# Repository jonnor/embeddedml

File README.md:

# Machine learning on embedded devices

Focused primarily on running inference/prediction/feed-forward part on a microcontroller (or small embedded device).
Training phase can run on a standard computer/server, using existing tools as much as possible.

# Background

## What and when to use machine learning

The defaults right now are to do conventional signal processing (no learning) in sensor,
and stream raw data to the cloud for storage and processing. Machine learning happens in the cloud.
If gateways are used, they mostly forward communication (no data processing). 

On-edge processing valueable when

* Local response needed. Autonomy
* Adaptable response needed. Over time, in context.
* Low/predictable latency needed
* Sending raw sensor data has privacy implications.
Audio, video.
* Unreliable connection
* High bandwidth sensor input.
Audio, video, accelerometer/IMU, current sensor, radiowaves.
* Low bandwidth algorithm output
* Events of interest are rare
* Low energy usage needed
* Full/raw sensor data is not valuable to store
* Sensor system should be low cost

Example usecases

* Predictive maintenance, using audio/vibration data
* Activitity detection for people, using audio/accelerometer data. Assistive tech, medical
* Appliance disaggregation, using aggregated power consumption data. "Non-Intrusive Load Monitoring" (NILM)
* Anomaly/change detection for predictive maintenance, using audio/vibration data, or electrical data
* Gesture recognition as human input device, using accelerometer/gyro data.
* Speech/command recognition as human input device, using microphone. Keyword/Wake-word detection
* Battery saving in wireless sensors. Normally sending day/week aggregates, on event/anomaly detection send data immediately
* Health status of animals via activity detected using accelerometer
* Monitoring eating activity using accelerometer [1](https://www.sciencedirect.com/science/article/pii/S0010482515000086)
* Environmental monitoring, using microphone to detect unwanted activity like cutting down trees
* Adaptive signalling and routing for wireless transmission in Wireless Sensor networks
* Electronic nose using arrays of MEMS detectors
* Material identification using reflecive spectrometer [1](https://hackaday.io/project/143014-compact-25-spectrometer/)

More notes on [Applications](./applications)

### Motivation

* [Why the Future of Machine Learning is Tiny (devices)](https://petewarden.com/2018/06/11/why-the-future-of-machine-learning-is-tiny)
Tiny Computers are Already Cheap and Everywhere. Energy is the Limiting Factor.We Capture Much More Sensor Data Than We Use.
* [embedded.com: Bringing machine learning to the edge](https://www.embedded.com/electronics-blogs/say-what-/4460873/Bringing-machine-learning-to-the-edge--A-Q-A-with-Neurala-s-Anatoli-Gorshechnikov-)
Predictions are much lower bandwidth than the raw sensor data (e.g. video)
It allows for local adaptation in the AI logic (L-DNN)
It achieves lower latency between observed event and action resulting from AI logic
"the most important question is what is the least amount accuracy and computation complexity we can do
while still delivering the business value?"
Top mistake: "Continuing with the top down approach ‘let’s make it perform the task first and then squeeze it on device`
instead of switching to bottom up ‘let’s make it run on device and fulfill all hardware constraints first,
and then tune it for the task at hand’."
* [How to run deep learning model on microcontroller with CMSIS-NN](https://www.dlology.com/blog/how-to-run-deep-learning-model-on-microcontroller-with-cmsis-nn/).
Why run deep learning model on a microcontroller?
Sensitive data gets to the cloud, photos, and audio recordings.
The company who sells this may charge a service fee to use its service and even worse sell your private data.
It won't work without the network connection to the server.
Data traveling back and forth between the device and server introduces lag.
Require network and wireless hardware components on the circuit design which increase the cost.
It might waste bandwidth sending useless data.

# Own contributions

Presentations

- [Embedding Data Science in IoT devices with MicroPython and emlearn](./presentations/euroscipy2026/presentation). EuroSciPy 2026, Krakow.
- [Machine Learning on Microcontrollers; Tiny, Useful and Fun](./presentations/ai-dev-europe-2025). Open Source GenAI & ML Summit. Amsterdam, August 2025.
- [Sensor data processing for scientific applications with MicroPython](./presentations/euroscipy2025/). EuroSciPy 2025, Krakow.
- [Machine Learning on Microcontrollers With Zephyr and emlearn](./presentations/open-source-summit-europe-2025). Open Source Summit / Zephyr Developer Summit. Amsterdam, August 2025.
- [Microcontrollers and Machine Learning with MicroPython and emlearn](./presentations/foss-north-2025). FOSS-North. Gothenburg, April 2025.
- [Sensor data processing on microcontrollers with MicroPython and emlearn](./presentations/PyConZA2024/). PyCon South Africa. Online, October 2024.
- [emlearn - Machine Learning for Tiny Embedded Systems](./presentations/EmbeddedOnlineConference2024). Embedded Online Conference. April 2024.
- [6 years of open source TinyML with emlearn](./presentations/TinymlEMEA2024). TinyML EMEA, Milano. June 2024.
- [emlearn - Machine Learning for Tiny Embedded Systems](./presentations/EmbeddedOnlineConference2024). May 2024.
- [Machine Learning on microcontrollers using MicroPython and emlearn](./presentations/PyDataBerlin2024/). PyDataBerlin & PyCon DE. April 2024.
- [HVAC monitoring in commercial buildings using Anomaly Detection](./presentations/TinymlAnomalyDetection2023/). TinyAI Forum on PdM and Anomaly Detection (online). December 2023.

Lecture notes

- [Practical TinyML with emlearn](./presentations/AarhusUniversity2026/). Aarhus University. March 2026.
- [emlearn @ TinyMLDays Aarhus](./presentations/TinyMLDays2025/). August 2025.

Open source software

- [emlearn](https://github.com/emlearn/emlearn). Machine Learning inference engine in C99 for Microcontrollers and Embedded devices. Since 2018.
- [emlearn-micropython](https://github.com/emlearn/emlearn-micropython). Efficient and convenient Machine Learning and DSP for MicroPython. Since 2024.

Fun projects

- Automatic toothbrush timer using accelerometer. [Github project](https://github.com/jonnor/toothbrush/). [Video presentation](https://www.youtube.com/watch?v=KkrfKPlnoZQ).
- Spectrometer for edible oils [Github project](https://github.com/jonnor/spectrometer/).

Commercial projects

- Acoustic detection of first crack in [Roest coffee roasting machines](https://www.roestcoffee.com/). Shipping since 2019.
[Tech presentation](https://www.youtube.com/watch?v=muZY1eCke40). 

# Learning material

Books

* [Learning in Embedded Systems](https://mitpress.mit.edu/books/learning-embedded-systems), May 1993.
* [TinyML: Machine Learning with TensorFlow on Arduino, and Ultra-Low Power Micro-Controllers](https://tinymlbook.com/). January, 2020.
* [TinyML Cookbook](https://www.packtpub.com/product/tinyml-cookbook/9781801814973).
* [Machine Learning Systems - Principles and Practices of Engineering Artificially Intelligent Systems](https://mlsysbook.ai/book/).

Articles

- [Embedded.com: Applying machine learning in embedded systems](https://www.embedded.com/applying-machine-learning-in-embedded-systems)
- [Embedded.com: Transfer learning for the IoT](https://www.embedded.com/transfer-learning-for-the-iot/)

# Tools

Open-source

* [emlearn](http://github.com/emlearn/emlearn). Inference engine for microcontrollers.
Supports converting scikit-learn models to plain C code.
No dynamic allocations. No runtime needed.
* [TensorFlow Lite for Microcontrollers](https://www.tensorflow.org/lite/microcontrollers).
Supports neural network models made with TensorFlow (including Keras).
Can run on wide range of platforms.
Since November 2018. Supports ARM Cortex M, RISC-V, ESP32/Xtensa and Linux/MacOS host.
Requires a runtime, aroud 20 kB.
* [onnx2c](https://github.com/kraiskil/onnx2c). Allows generating C code from ONNX models.
* [iree](https://iree.dev/guides/deployment-configurations/bare-metal/). Compiler. Has bare metal target. Around 30 kB runtime.
* [executorch](https://github.com/pytorch/executorch).
C++ framework for deploying PyTorch models. Focused on custom backends, NPUs etc. Microcontroller CPU less in focus.
Around 50 kB runtime. Supports bare-metal via "Portable" operations, or specialized for Cortex M.
* [nnom](https://github.com/majianjia/nnom) - Fixed-point neural network compiler for microcontrollers.
Supports wide range of networks. Outputs plain C code. Can use CMSIS-NN on ARM Cortex M.
* [Embedded Learning Library](https://github.com/Microsoft/ELL) by Microsoft. Discontinued in 2024
Set of C++ libraries for machine learning on embedded platforms. Includes code for kNN, RandomForest etc.
Also has some node-based dataflow system in place it seems. JavaScript and Python bindings.
* [uTensor](https://github.com/uTensor/uTensor).
Export Tensorflow model to mbed/ARM microcontrollers.
Not supported on ESP32 or RISC-V or similar. Lower activity since 2021.
- [sklearn-porter](https://github.com/nok/sklearn-porter).
Can compile DecisionTreeClassifier and SVC models to C.
Uses dynamic memory.
Not optimized for use on embedded devices.
* [microTVM](https://tvm.apache.org/docs/topic/microtvm/index.html).
Depends only on the C standard library, and runs bare metal such as STM32 and NRF52 microcontrollers.
Is under development. Which models are supported on microcontrollers not specified.

Low-level libraries

* [gemmlowp](https://github.com/google/gemmlowp).
Low-precision matrix multiplication. Only general matrix multiplication ("GEMM"). C++11
* [CMSIS-NN](https://github.com/ARM-software/CMSIS-NN). Neural network operations for ARM Cortex M.
* [esp-nn](https://github.com/espressif/esp-nn). Neural Network functions Espressif ESP32 (Xtensa and RISC-V).
* . Can be used bare-metal, but more focused on mobile/server grade (Cortex A+ etc).

Proprietary

* X-CUBE-AI for STM32

Historical

- [nn4mc_cpp](https://github.com/correlllab/nn4mc_cpp).
Neural Networks for Microcontrollers.
Supports Keras natively. Provides instructions for PyTorch et.c via ONNX.
Documentation for using from Python is lacking, as well as the type of networks supported.
Does not seem maintained since 2020.
* [Embedded Classification Software Toolbox](https://github.com/ma2th/ecst).
Unmaintained since 2018.
* ONNC project has a [backend for ARM Cortex M](https://github.com/ONNC/onnc-tutorial/blob/master/lab_2_Digit_Recognition_with_ARM_CortexM/lab_2.md) (using CMSIS-NN)
and a [C backend](https://github.com/ONNC/onnc/blob/74e59908b2881844329c3d330eea7a7c306e1e22/docs/ONNC-C-Backend-Guide.md).
Allows to convert an ONNX models to run on devices.
Not updated since 2021.
- [micromlgen](https://github.com/eloquentarduino/micromlgen).
Generate C code for microcontrollers from Python's sklearn classifiers.
Archived in 2024.

# Models

A range of Machine Learning models are useful in an embedded devices setting.
Classical methods are used when the amount of data is quite small,
and neural networks for large datasets and complex inputs.

Below are notes on the various models in the context of embedded Machine Learning,
including model size and compute-time optimization.

- [Tree-based methods](./models/tree-based.md).
Random Forest, Extratrees, Decision Trees, et.c.
- [Neural Networks](./models/neural-networks.md).
Convolutional Neural Networks (CNN), Recurrent Neural Networks (RNN), Autoencoders
- [Support Vector Machines](./models/support-vector-machine.md) (SVM).
- [Mixture models](./models/mixtures.md).
Gaussian Mixture Models (GMM).
- [Nearest Neighbours](./models/k-nearest-neighbours.md). kNN et.c.

# More topics

- [Privacy](./topics/privacy.md)
- [Energy usage](./topics/energy-usage.md)
- [Model size](./topics/model-size.md)
- [On-device learning](./on-device-learning)

## State of the Art in 2019
Of ML inference on general-purpose microcontrollers.

```
TODO: update for 2023
```

- Deep models have efficient implementations for ARM Cortex-M. Ex: CNN and RNN in CMSIS-NN, FC in uTensor
- Some implementations available for non-neural models that *can* be used. Ex: SVM,RF,AdaBoost in sklearn-porter
- A few special-designed ML algorithms made. Ex: ProtoNN, Bonsai
- Basic tools available for converting Tensorflow models
- Keyword-spotting/wake-word on audio well established. Used in commercial products (Alexa etc)
- Human activity detecton on accelerometers.
- Computer vision is actively developed
- Lots of research and many announcements of low-power co-processors, but little on market yet

Limitations

- Neural models lacking for non-ARM micros. ESP8266/ESP32
- Non-neural models missing inference engines designed for microcontrollers
- "Small DNN" work mostly on computer vision for mobile phones (model size 1000x of uC)
- Few/no pretrained models available. Transfer learning little explored?
- Very little documentation of entire development process.
From planning, data aquisition, model design
- Best practices underdocumented (or underdeveloped?) 

Ways of advancing, make contributions

- Faster inference. Power saving, or bigger problems.
- Smaller models. Cheaper MCU, or bigger problems.
- Better accuracy on a problem. Better user experience, new usecases
- Solve a concrete usecase. Easier to deploy similar usecases
- Comparison between approaches. Microcontroller, ML model
- Libraries or tools. Lower time to market, enable more developers

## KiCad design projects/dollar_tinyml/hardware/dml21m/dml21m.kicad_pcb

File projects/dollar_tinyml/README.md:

# 1 dollar TinyML

A computer with a modern GPU for machine learning is approx 1000 USD.
The state-of-the-art ML models that in the mainstream attention are getting ever larger.
Currently being led by Large Language Models and Generative Image models.
Requiring more compute and RAM every year.

TinyML is a whole nother beast
- with a focus on tiny models that can run on small,power-efficient and low-cost microcontrollers.
Low cost enables massive scale.

Taking this to an extreme, this project raises the question

> Can one build a whole TinyML enabled sensor for under 1 USD?

## Current status

**Feasibility research done. Prototyping hardware+software**.

- Initial system architecture decided. See below
- Feasibility research documented under [references](./references)

There are also notes about next steps in [TODO](./TODO.md)

## See also

You can also follow [this project on Hackaday.io](https://hackaday.io/project/194511-1-dollar-tinyml).

## Scope and limitations

We consider total costs as the Bill-of-Materials (BOM) for a useful system.

- The system must perform a useful function
- System should be able to work stand-alone
- Reliance on external items must be limited to items that any consumer can be expected to have already
Example: smartphone, USB charger, PC
- PCB Assembly (PCBA) costs are not included
- Mechanical elements apart from PCB not included
- Assuming production volume of 1000 units

## System architecture

Key functionality

- Capture and process motion/vibration data (from accelerometers)
- Capture and process audio data (from microphone)
- Running classification algorithms such as decision tree ensembles and recurrent neural networks
- Transmit results using BLE advertisements

Example usecases

- Human Activity Detection
- Sound Event Detection
- Voice/Speech Activity Detection

Components

```
Microcontroller                 PY32F003A
MEMS accelerometer.             ST LIS2DH12
MEMS microphone (analog)        LinkMEMS LMA2718
Bluetooth Low Energy beacon     Holtek BC7161
Battery                         LIR1220, charger included
External power                  USB Type A (PCB edge connector)
```

BOM for core components `0.90 USD`.
This leaves `0.10 USD` for jellybeans (standard capacitors/resistors).
Possible to drop either the microphone+opamp (0.12 USD) or accelerometer (0.26 USD).
Should also be possible to drop the battery (0.25 USD), if running on USB power.

[Bill of Materials](hardware/dml10/BOM.csv).

## Related projects

[emlearn](https://emlearn.org), a Machine Learning engine in C99, designed for tiny microcontroller and embedded systems.

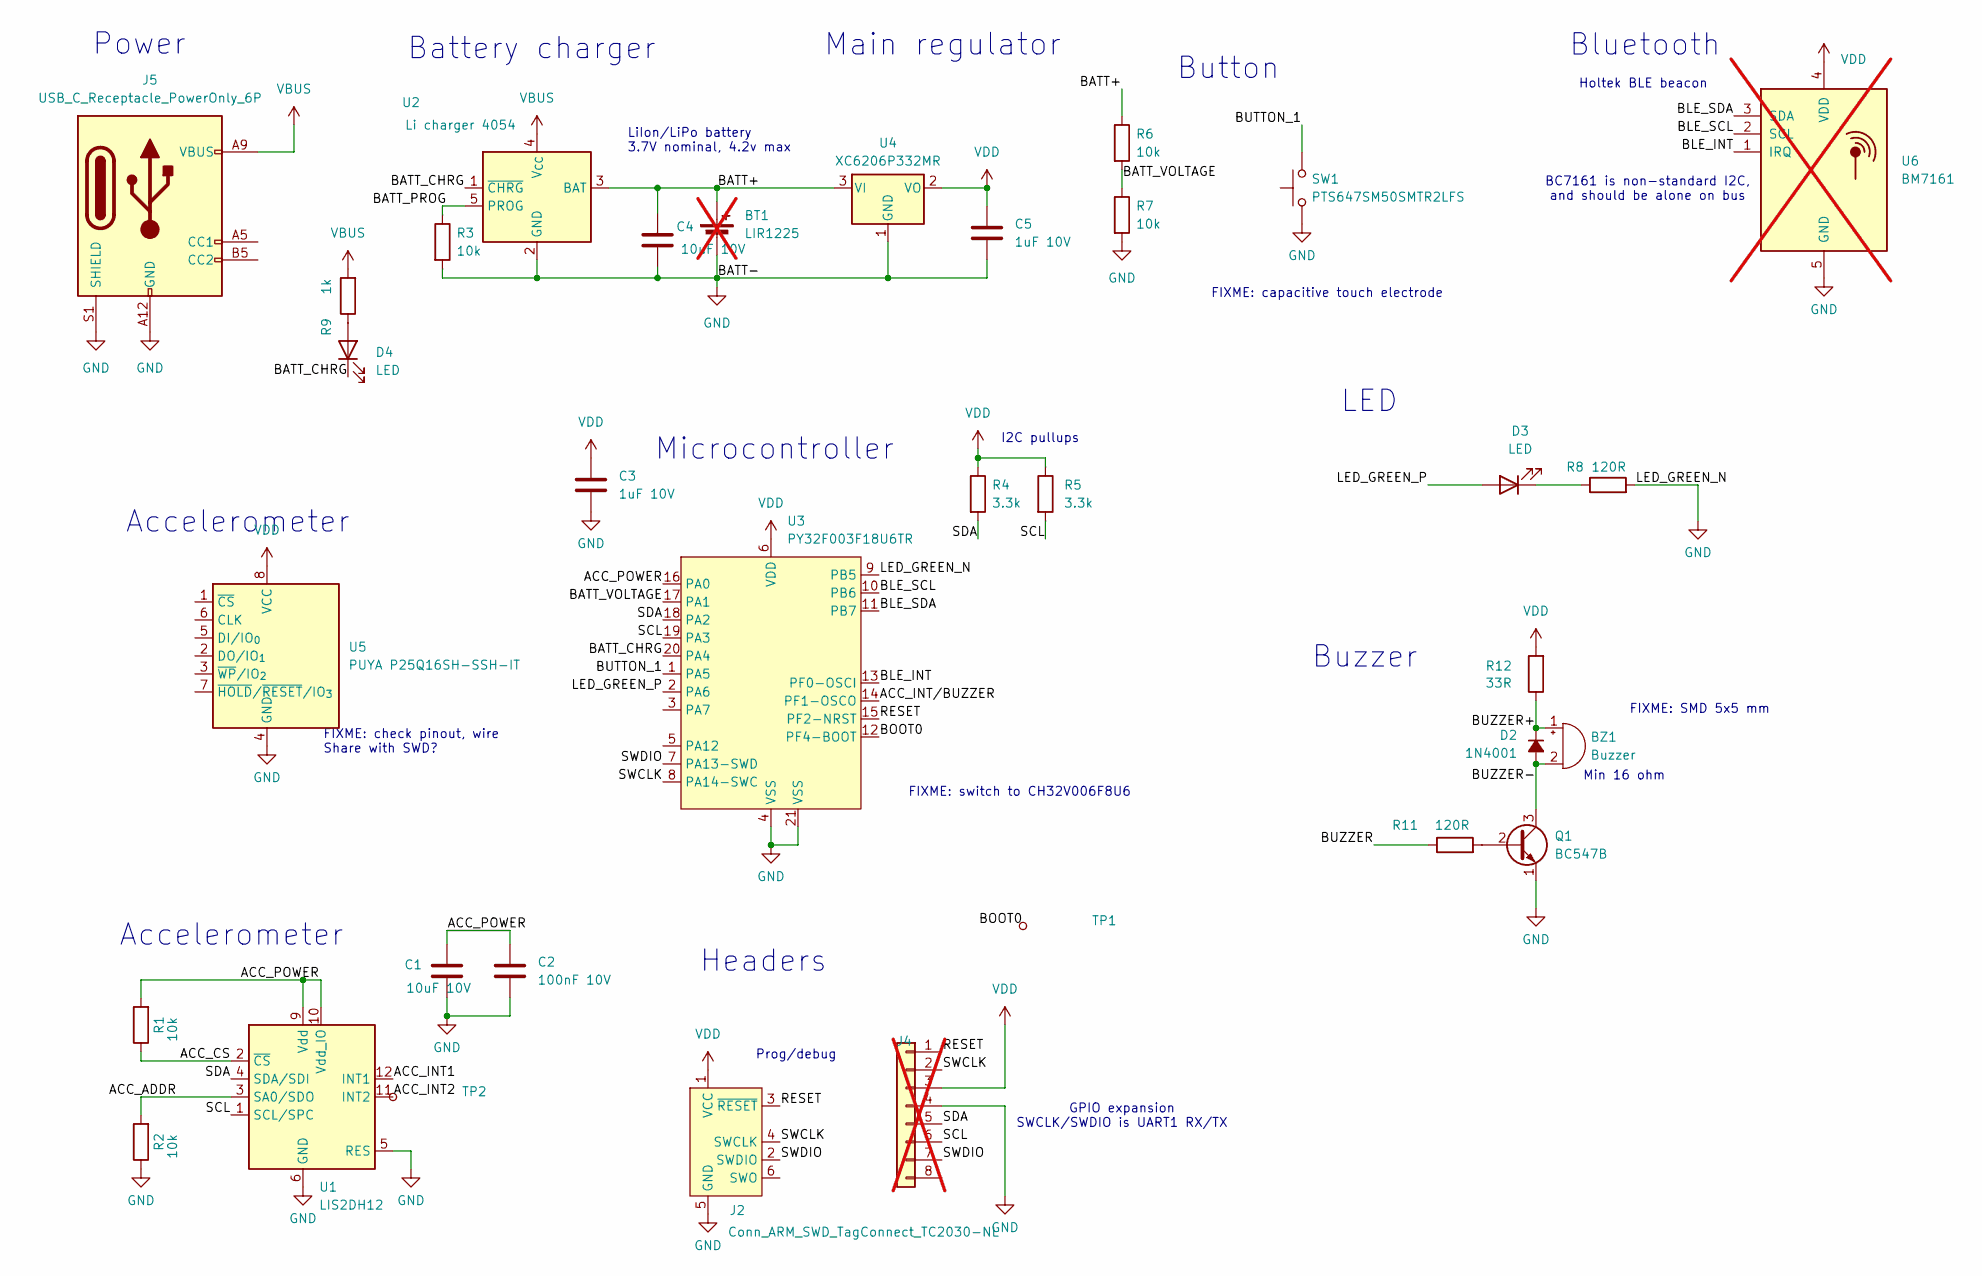
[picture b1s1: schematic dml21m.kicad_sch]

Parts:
BT1: LIR1225; Battery_CR1220-Horizontal; not fitted
BZ1: Buzzer; Buzzer_Murata_PKMCS0909E
C1, C4: 10uF 10V; C_0402_1005Metric
C2: 100nF 10V; C_0402_1005Metric
C3, C5: 1uF 10V; C_0402_1005Metric
D2: 1N4001; D_SOD-323
D3, D4: LED; LED_0402_1005Metric
J2: Conn_ARM_SWD_TagConnect_TC2030-NL; Tag-Connect_TC2030-IDC-NL_2x03_P1.27mm_Vertical
J4: Header 2.54mm; JST_SH_SM08B-SRSS-TB_1x08-1MP_P1.00mm_Horizontal; not fitted
J5: USB_C_Receptacle_PowerOnly_6P; USB_C_Receptacle_GCT_USB4125-xx-x_6P_TopMnt_Horizontal
Q1: BC547B; SOT-23
R1, R2, R3, R6, R7: 10k; R_0402_1005Metric
R4, R5: 3.3k; R_0402_1005Metric
R8, R11: 120R; R_0402_1005Metric
R9: 1k; R_0402_1005Metric
R12: 33R; R_0402_1005Metric
SW1: PTS647SM50SMTR2LFS; SolderJumper-2_P1.3mm_Open_Pad1.0x1.5mm; MPN PTS647SM50SMTR2LFS
TP1, TP2: TP_PCB; TestPoint_Pad_D1.0mm
U1: LIS2DH12; LGA-12_2x2mm_P0.5mm; MPN LIS2DH12TR
U2: Li charger 4054; TSOT-23-5; MPN LP4054HB5F
U3: PY32F003F18U6TR; QFN-20-1EP_3x3mm_P0.4mm_EP1.65x1.65mm; MPN PY32F003F18U6TR
U4: XC6206P332MR; SOT-23-3; MPN XC6206P332MR
U5: PUYA P25Q16SH-SSH-IT; SOIC-8_5.3x5.3mm_P1.27mm
U6: BM7161; not fitted

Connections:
/ACC_ADDR: R2.2, U1.3 (SA0/SDO)
/ACC_CS: R1.1, U1.2 (~CS)
/ACC_INT1: U1.12 (INT1)
/ACC_INT2: TP2.1, U1.11 (INT2)
/ACC_INT/BUZZER: U3.14 (PF1-OSCO)
/ACC_POWER: C1.1, C2.1, R1.2, U1.9 (Vdd), U1.10 (Vdd_IO), U3.16 (PA0)
/BATT+: BT1.1 (+), C4.1, R6.1, U2.3 (BAT), U4.3 (VI)
/BATT_CHRG: D4.1 (K), U2.1 (~CHRG), U3.20 (PA4)
/BATT_PROG: R3.1, U2.5 (PROG)
/BATT_VOLTAGE: R6.2, R7.1, U3.17 (PA1)
/BLE_INT: U3.13 (PF0-OSCI), U6.1 (IRQ)
/BLE_SCL: U3.10 (PB6), U6.2 (SCL)
/BLE_SDA: U3.11 (PB7), U6.3 (SDA)
/BOOT0: TP1.1, U3.12 (PF4-BOOT)
/BUTTON_1: SW1.2, U3.1 (PA5)
/BUZZER: R11.1
/BUZZER+: BZ1.1 (+), D2.1 (K), R12.1
/BUZZER-: BZ1.2 (-), D2.2 (A), Q1.3 (C)
/LED_GREEN_P: D3.2 (A), U3.2 (PA6)
/RESET: J2.3 (~RESET), J4.1, U3.15 (PF2-NRST)
/SCL: J4.6, R5.2, U1.1 (SCL/SPC), U3.19 (PA3)
/SDA: J4.5, R4.2, U1.4 (SDA/SDI), U3.18 (PA2)
/SWCLK: J2.4 (SWCLK), J4.2, U3.8 (PA14-SWC)
/SWDIO: J2.2 (SWDIO), J4.7, U3.7 (PA13-SWD)
GND: BT1.2 (-), C1.2, C2.2, C3.1, C4.2, C5.1, J2.5 (GND), J4.4, J5.A12 (GND), J5.B12 (GND), J5.S1 (SHIELD), Q1.1 (E), R2.1, R3.2, R7.2, R8.2, SW1.1, U1.5 (RES), U1.6 (GND), U1.7 (GND), U1.8 (GND), U2.2 (GND), U3.4 (VSS), U3.9 (PB5), U3.21 (VSS), U4.1 (GND), U5.4 (GND), U6.5 (GND)
unnamed: D3.1 (K), R8.1
unnamed: D4.2 (A), R9.1
unnamed: Q1.2 (B), R11.2
VBUS: J5.A9 (VBUS), J5.B9 (VBUS), R9.2, U2.4 (V_{CC})
VDD: C3.2, C5.2, J2.1 (VCC), J4.3, R4.1, R5.1, R12.2, U3.6 (VDD), U4.2 (VO), U5.8 (VCC), U6.4 (VDD)

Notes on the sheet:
Buzzer
Prog/debug
Main regulator
Min 16 ohm
Microcontroller
FIXME: SMD 5x5 mm
Button
Holtek BLE beacon
GPIO expansion SWCLK/SWDIO is UART1 RX/TX
Power
LiIon/LiPo battery 3.7V nominal, 4.2v max
FIXME: check pinout, wire Share with SWD?
FIXME: capacitive touch electrode
Accelerometer
I2C pullups
Headers
LED
Bluetooth
BC7161 is non-standard I2C, and should be alone on bus
FIXME: switch to CH32V006F8U6
Battery charger

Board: 2 copper layers, 34 parts (7 on the bottom side), 27 nets, no tracks yet.

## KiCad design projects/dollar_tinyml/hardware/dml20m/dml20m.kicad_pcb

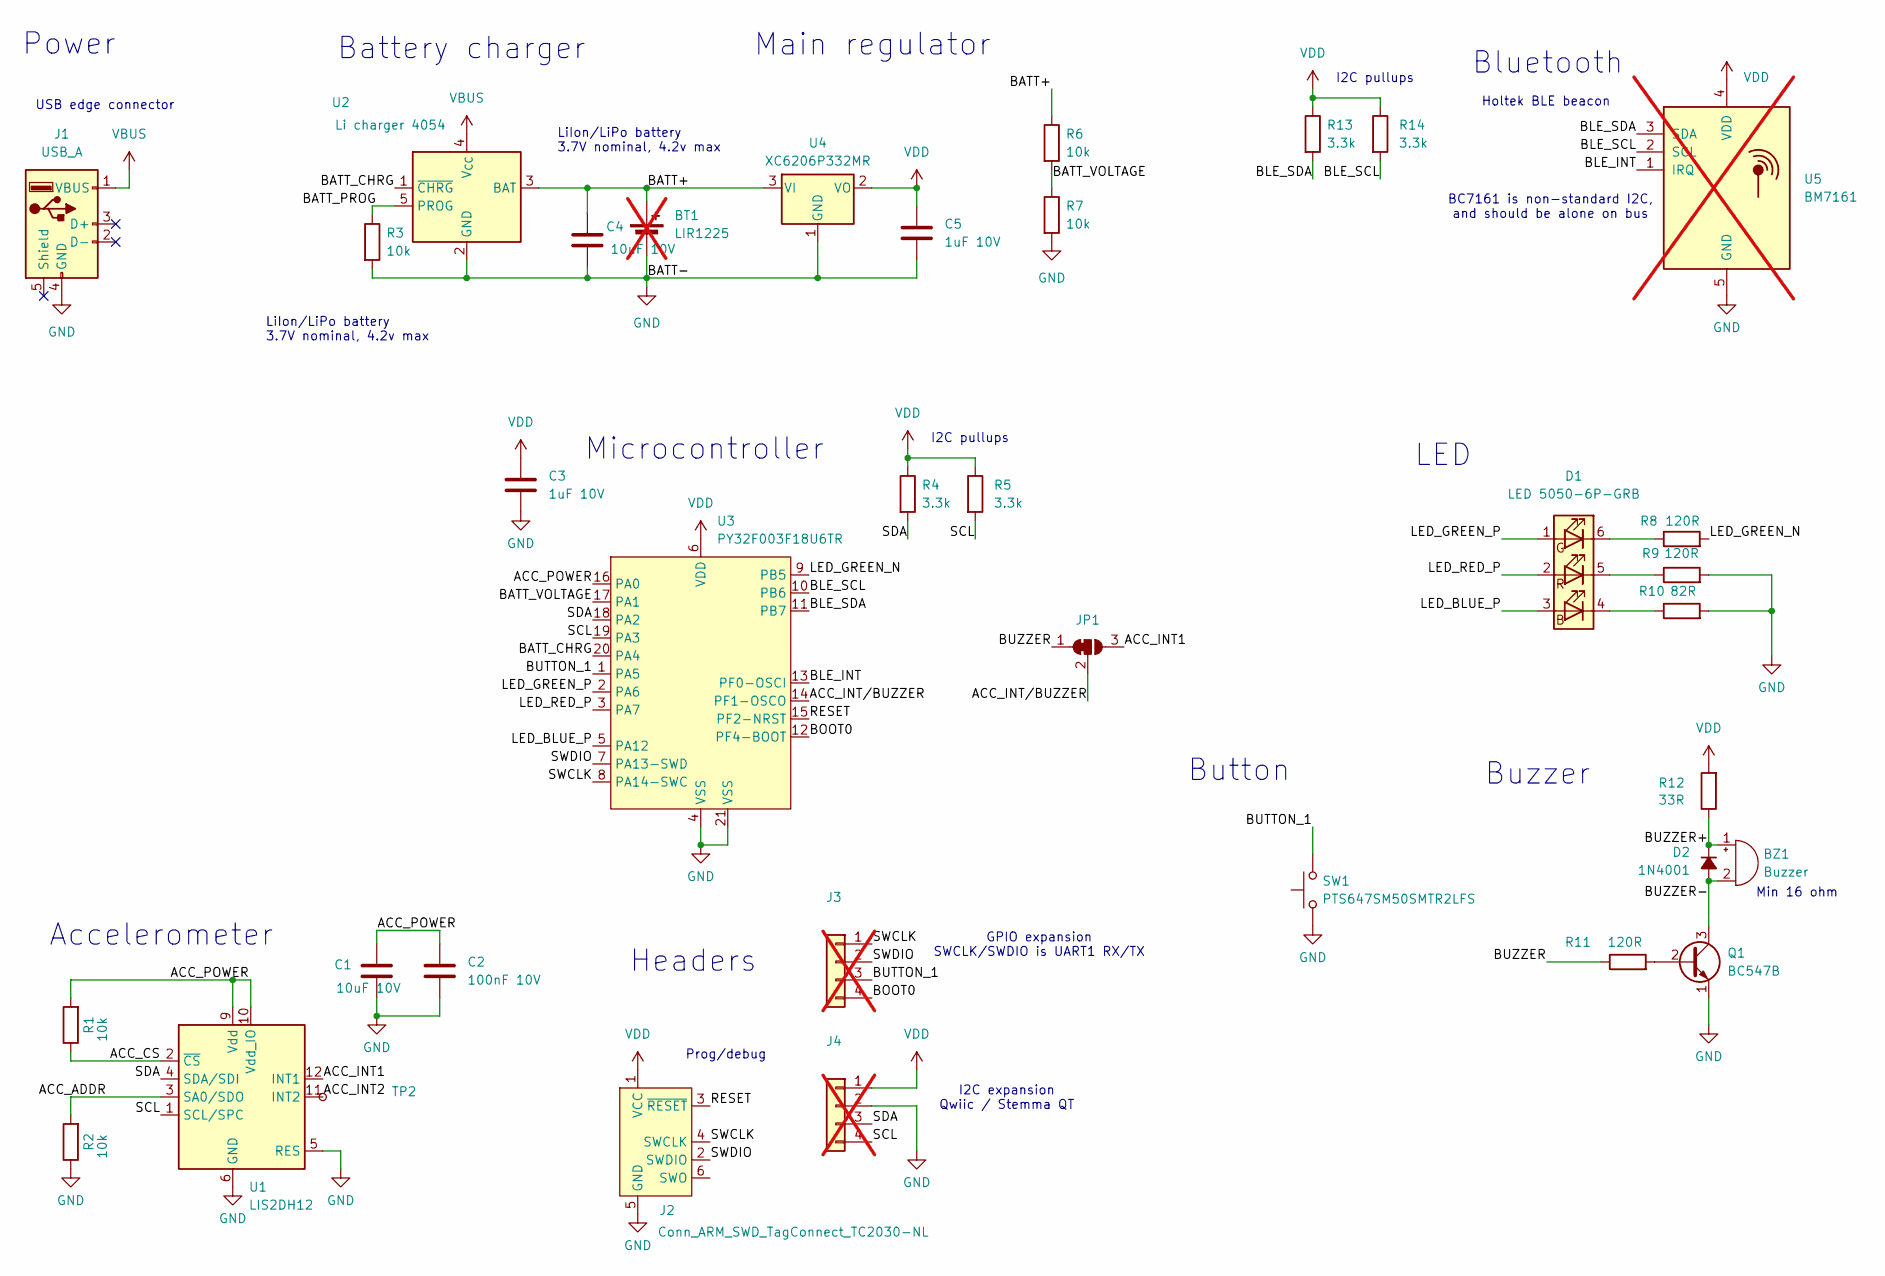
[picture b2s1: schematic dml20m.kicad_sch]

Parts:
BT1: LIR1225; Battery_CR1220-Horizontal; not fitted
BZ1: Buzzer; SolderJumper-2_P1.3mm_Open_Pad1.0x1.5mm
C1, C4: 10uF 10V; C_0603_1608Metric
C2: 100nF 10V; C_0603_1608Metric
C3, C5: 1uF 10V; C_0603_1608Metric
D1: LED 5050-6P-GRB; LED_RGB_5050-6; MPN TC5050RGBF08-3CJH-AF53A
D2: 1N4001; D_SOD-123F
J1: USB_A; EdgeUSBTypeA
J2: Conn_ARM_SWD_TagConnect_TC2030-NL; Tag-Connect_TC2030-IDC-NL_2x03_P1.27mm_Vertical
J3, J4: Header 2.54mm; JST_SH_SM04B-SRSS-TB_1x04-1MP_P1.00mm_Horizontal; not fitted
JP1: SolderJumper_3_Bridged12; SolderJumper-3_P1.3mm_Bridged12_RoundedPad1.0x1.5mm
Q1: BC547B; SOT-23
R1, R2, R3, R6, R7: 10k; R_0603_1608Metric
R4, R5, R13, R14: 3.3k; R_0603_1608Metric
R8, R9, R11: 120R; R_0603_1608Metric
R10: 82R; R_0603_1608Metric
R12: 33R; R_0603_1608Metric
SW1: PTS647SM50SMTR2LFS; SW_SPST_PTS647_Sx38; MPN PTS647SM50SMTR2LFS
TP2: TP_PCB; TestPoint_Pad_D1.0mm
U1: LIS2DH12; LGA-12_2x2mm_P0.5mm; MPN LIS2DH12TR
U2: Li charger 4054; TSOT-23-5; MPN LP4054HB5F
U3: PY32F003F18U6TR; QFN-20-1EP_3x3mm_P0.4mm_EP1.65x1.65mm; MPN PY32F003F18U6TR
U4: XC6206P332MR; SOT-23-3; MPN XC6206P332MR
U5: BM7161; not fitted

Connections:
/ACC_ADDR: R2.2, U1.3 (SA0/SDO)
/ACC_CS: R1.1, U1.2 (~CS)
/ACC_INT1: JP1.3 (B), U1.12 (INT1)
/ACC_INT2: TP2.1, U1.11 (INT2)
/ACC_INT/BUZZER: JP1.2 (C), U3.14 (PF1-OSCO)
/ACC_POWER: C1.1, C2.1, R1.2, U1.9 (Vdd), U1.10 (Vdd_IO), U3.16 (PA0)
/BATT+: BT1.1 (+), C4.1, R6.1, U2.3 (BAT), U4.3 (VI)
/BATT_CHRG: U2.1 (~CHRG), U3.20 (PA4)
/BATT_PROG: R3.1, U2.5 (PROG)
/BATT_VOLTAGE: R6.2, R7.1, U3.17 (PA1)
/BLE_INT: U3.13 (PF0-OSCI), U5.1 (IRQ)
/BLE_SCL: R14.2, U3.10 (PB6), U5.2 (SCL)
/BLE_SDA: R13.2, U3.11 (PB7), U5.3 (SDA)
/BOOT0: J3.4, U3.12 (PF4-BOOT)
/BUTTON_1: J3.3, SW1.2, U3.1 (PA5)
/BUZZER: JP1.1 (A), R11.1
/BUZZER+: BZ1.1 (+), D2.1 (K), R12.1
/BUZZER-: BZ1.2 (-), D2.2 (A), Q1.3 (C)
/LED_BLUE_P: D1.3 (BK), U3.5 (PA12)
/LED_GREEN_N: R8.2, U3.9 (PB5)
/LED_GREEN_P: D1.1 (RK), U3.2 (PA6)
/LED_RED_P: D1.2 (GK), U3.3 (PA7)
/RESET: J2.3 (~RESET), U3.15 (PF2-NRST)
/SCL: J4.4, R5.2, U1.1 (SCL/SPC), U3.19 (PA3)
/SDA: J4.3, R4.2, U1.4 (SDA/SDI), U3.18 (PA2)
/SWCLK: J2.4 (SWCLK), J3.1, U3.8 (PA14-SWC)
/SWDIO: J2.2 (SWDIO), J3.2, U3.7 (PA13-SWD)
GND: BT1.2 (-), C1.2, C2.2, C3.1, C4.2, C5.1, J1.4 (GND), J2.5 (GND), J4.2, Q1.1 (E), R2.1, R3.2, R7.2, R9.2, R10.2, SW1.1, U1.5 (RES), U1.6 (GND), U1.7 (GND), U1.8 (GND), U2.2 (GND), U3.4 (VSS), U3.21 (VSS), U4.1 (GND), U5.5 (GND)
unnamed: D1.4 (BA), R10.1
unnamed: D1.5 (GA), R9.1
unnamed: D1.6 (RA), R8.1
unnamed: Q1.2 (B), R11.2
VBUS: J1.1 (VBUS), U2.4 (V_{CC})
VDD: C3.2, C5.2, J2.1 (VCC), J4.1, R4.1, R5.1, R12.2, R13.1, R14.1, U3.6 (VDD), U4.2 (VO), U5.4 (VDD)

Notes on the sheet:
Buzzer
Prog/debug
Main regulator
Min 16 ohm
Microcontroller
Button
GPIO expansion SWCLK/SWDIO is UART1 RX/TX
Power
LiIon/LiPo battery 3.7V nominal, 4.2v max
Accelerometer
I2C pullups
USB edge connector
Headers
LED
Holtek BLE beacon
I2C expansion Qwiic / Stemma QT
Bluetooth
BC7161 is non-standard I2C, and should be alone on bus
Battery charger

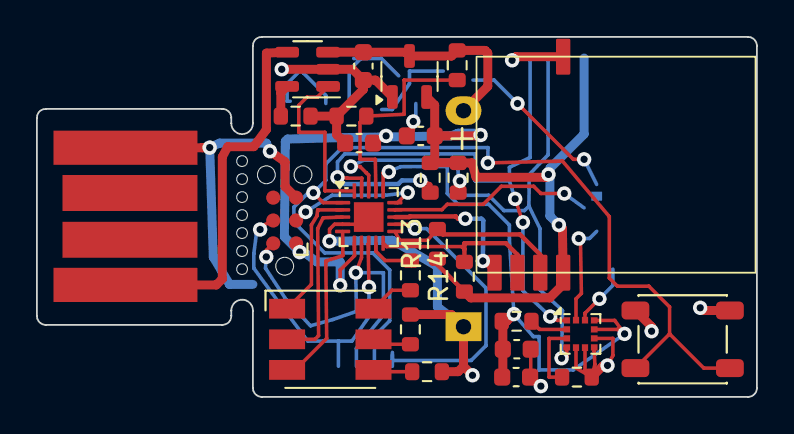
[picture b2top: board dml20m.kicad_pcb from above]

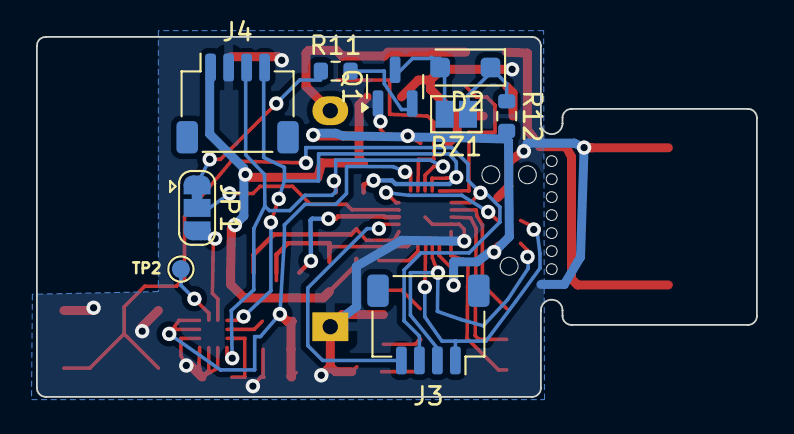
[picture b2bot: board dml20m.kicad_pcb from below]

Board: 2 copper layers, 40.0 x 20.0 mm, 37 parts (9 on the bottom side), 34 nets.

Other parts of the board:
H1: MountingHole; Mousebite_0.6mmX8

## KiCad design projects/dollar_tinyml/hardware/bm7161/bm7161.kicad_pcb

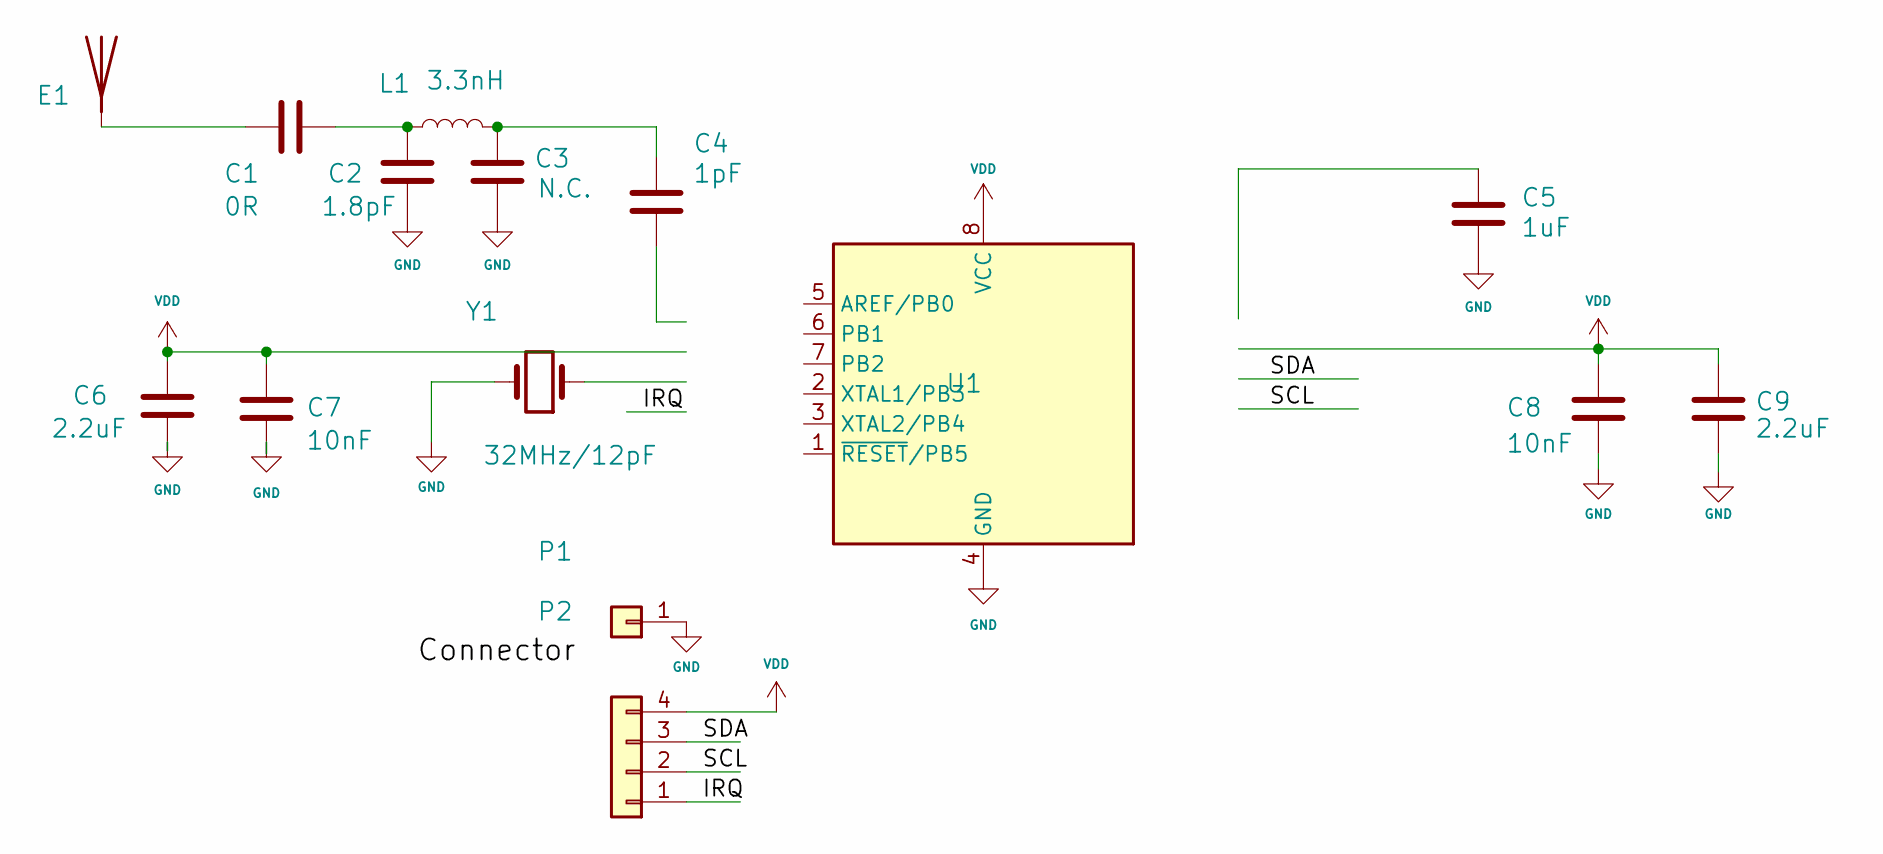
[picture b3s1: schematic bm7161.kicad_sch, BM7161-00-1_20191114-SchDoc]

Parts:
C1: 0R; C_0402_1005Metric
C2: 1.8pF; C_0402_1005Metric
C3: N.C.; C_0402_1005Metric
C4: 1pF; C_0402_1005Metric
C5: 1uF; C_0402_1005Metric
C6, C9: 2.2uF; C_0402_1005Metric
C7, C8: 10nF; C_0402_1005Metric
E1: (no value)
L1: 3.3nH; L_0402_1005Metric
P1, P2: (no value)
U1: SOIC-8W_5.3x5.3mm_P1.27mm
Y1: 32MHz/12pF; Crystal_SMD_Abracon_ABM8G-4Pin_3.2x2.5mm

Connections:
GND: C2.2, C3.2, C5.1, C6.1, C7.2, C8.2, C9.2, P1.1, U1.4 (GND), Y1.2; also elsewhere on the board
IRQ: P2.1
unnamed: C1.2, C2.1, L1.1
unnamed: C3.1, C4.1, L1.2
unnamed: C1.1, E1.1
SCL: P2.2
SDA: P2.3
VDD: C6.2, C7.1, C8.1, C9.1, P2.4, U1.8 (VCC)

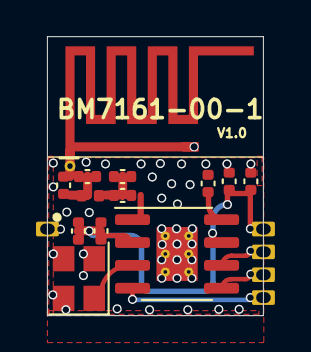
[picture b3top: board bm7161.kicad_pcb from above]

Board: 2 copper layers, 12.0 x 15.5 mm, 16 parts (1 on the bottom side), 4 nets.

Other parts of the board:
Designator6: Comment; _Users_zhengzicong_Desktop_10DFN_BM7161-00-1.PcbLib_logo_0.8
Designator16: Comment; 2.4G_B_6_4

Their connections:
GND: Designator16.2; also elsewhere on the board

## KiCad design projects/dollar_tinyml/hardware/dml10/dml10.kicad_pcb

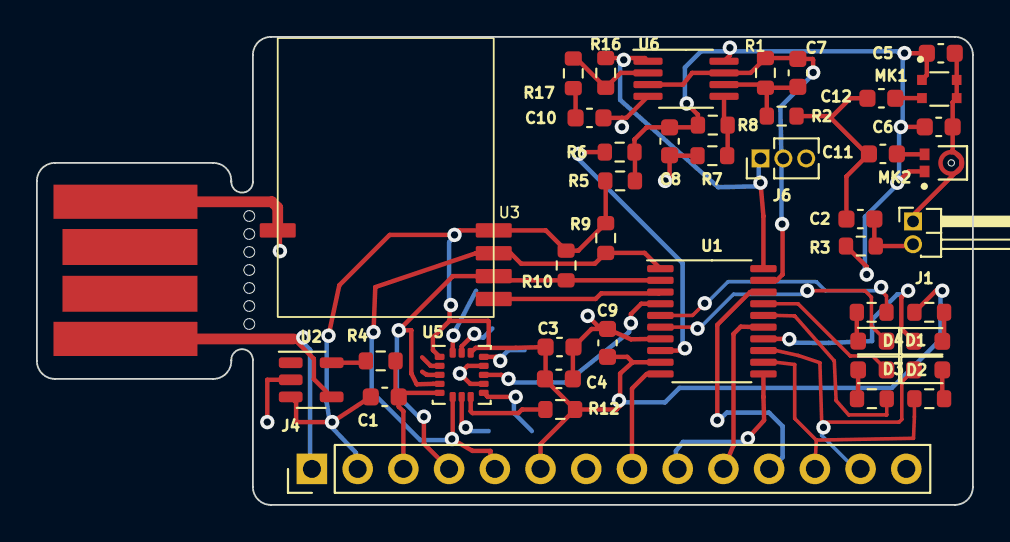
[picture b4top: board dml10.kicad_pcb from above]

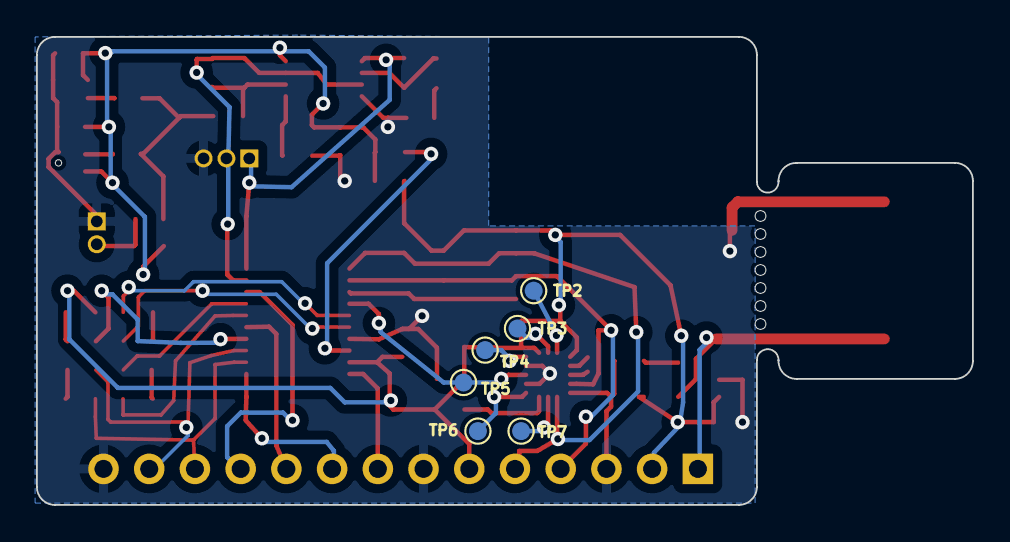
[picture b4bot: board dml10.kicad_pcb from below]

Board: 2 copper layers, 52.0 x 26.0 mm, 51 parts (6 on the bottom side), 41 nets.

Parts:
C1, C2, C4, C8, C10, C11, C12: 10uF 10V; C_0603_1608Metric
C3: 100nF 10V; C_0603_1608Metric
C5, C6, C9: 1uF 10V; C_0603_1608Metric
C7: 100pF 10V; C_0603_1608Metric
D1: CLEAR RED; LED_0603_1608Metric
D2: CLEAR GREEN; LED_0603_1608Metric
D3: CLEAR BLUE; LED_0603_1608Metric
D4: CLEAR WHITE; LED_0603_1608Metric
H1: MountingHole; Mousebite_0.6mmX8
J1: Header 2.54mm; PinHeader_1x02_P1.27mm_Horizontal
J2: USB_A; EdgeUSBTypeA
J4: Header 2.54mm; PinHeader_1x14_P2.54mm_Vertical
J6: Conn_01x03; PinHeader_1x03_P1.27mm_Vertical
MK1: LMA2718T421-OA5; XDCR_CMM-2718AT-42308-TR
MK2: LMA2718B381-OA5-2; XDCR_CMM-2718AB-383161-TR
R1, R16: 68k; R_0603_1608Metric
R2, R9, R10, R17: 3.3k; R_0603_1608Metric
R3: 3k3; R_0603_1608Metric
R4, R7, R8, R12: 10k; R_0603_1608Metric
R5, R6: 0R; R_0603_1608Metric
R11, R13: 120R; R_0603_1608Metric
R14, R15: 82R; R_0603_1608Metric
TP2, TP3, TP4, TP5, TP6, TP7: TP_PCB; TestPoint_Pad_D1.0mm
U1: PY32F003F16P6TU; TSSOP-20_4.4x6.5mm_P0.65mm
U2: LP4054HB5F; TSOT-23-5
U3: BM7161
U5: LIS3DH; LGA-16_3x3mm_P0.5mm_LayoutBorder3x5y
U6: GS8632-MR; MSOP-8_3x3mm_P0.65mm

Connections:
/ACC_ADC1: TP2.1, U5.16 (ADC1)
/ACC_ADC2: TP3.1, U5.15 (ADC2)
/ACC_ADC3: TP4.1, U5.13 (ADC3)
/ACC_ADDR: TP7.1, U5.7 (SDO/SA0)
/ACC_CS: R12.1, U5.8 (CS)
/ACC_INT1: TP5.1, U1.4 (PA5), U5.11 (INT1)
/ACC_INT2: TP6.1, U5.9 (INT2)
/AUDIO_HIGH: J6.1, R16.1, U1.20 (PA1), U6.1
/AUDIO_LOW: C7.2, J6.2, R1.2, U1.19 (PA0), U6.3 (+), U6.7
/BLE_INT: U1.3 (PA4), U3.1 (IRQ)
/BOOT0: J4.10, U1.15 (PF4-BOOT)
/LED_BLUE_N: D3.1 (K), J4.13, U1.13 (PB6)
/LED_BLUE_P: J4.12, R14.1, U1.12 (PB5)
/LED_GREEN_N: D2.1 (K), U1.17 (PF1-OSCO)
/LED_GREEN_P: R13.1, U1.16 (PF0-OSCI)
/LED_RED_N: D1.1 (K), U1.6 (PA7)
/LED_RED_P: R11.1, U1.5 (PA6)
/LED_WHITE_N: D4.1 (K), U1.14 (PB7)
/MIC_INPUT: C2.1, C11.1, C12.1, R2.1
/MIC_POWER: C5.1, C6.1, C8.2, MK1.1 (VDD), MK2.1 (VDD), R3.1, R5.2, R6.2, R8.2, U6.8 (V+)
/MIC_POWER_CTRL: R6.1, U1.8 (PA12)
/MIC_VREF: R7.2, R8.1, U6.5 (+)
/RESET: J4.11, U1.18 (PF2-NRST)
/SCL: J4.4, R10.2, U1.2 (PA3), U3.2 (SCL), U5.4 (SCL/SPC)
/SDA: J4.5, R9.2, U1.1 (PA2), U3.3 (SDA), U5.6 (SDA/SDI/SDO)
/SWCLK: J4.9, U1.11 (PA14)
/SWDIO: J4.8, U1.10 (PA13)
GND: C1.2, C3.2, C4.2, C5.2, C6.2, C8.1, C9.1, C10.2, J1.1, J2.4 (GND), J4.3, J4.7, J4.14, J6.3, MK1.2 (GND), MK1.3 (GND), MK2.3 (GND), R4.2, R7.1, U1.7 (VSS), U2.2 (GND), U3.5 (GND), U5.5 (GND), U5.10 (GND), U5.12 (GND), U6.4 (V-)
unnamed: C10.1, R17.2
unnamed: D1.2 (A), R11.2
unnamed: D2.2 (A), R13.2
unnamed: D3.2 (A), R14.2
unnamed: D4.2 (A), R15.2
unnamed: C2.2, J1.2, R3.2
unnamed: C12.2, MK1.4 (OUT)
unnamed: C11.2, MK2.2 (OUT)
unnamed: R4.1, U2.5 (PROG)
unnamed: R16.2, R17.1, U6.2 (-)
unnamed: C7.1, R1.1, R2.2, U6.6 (-)
VBUS: J2.1 (VBUS), J4.1, U2.4 (V_{CC})
VDD: C1.1, C3.1, C4.1, C9.2, J4.2, J4.6, R5.1, R9.1, R10.1, R12.2, R15.1, U1.9 (VDD), U2.3 (BAT), U3.4 (VDD), U5.1 (VDD_IO), U5.14 (VDD)

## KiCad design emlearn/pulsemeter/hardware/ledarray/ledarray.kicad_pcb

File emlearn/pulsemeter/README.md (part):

Sensor principle is measuring reflected/absorbed light
Easy with dedicated electronics.
https://lastminuteengineers.com/pulse-sensor-arduino-tutorial/

Can it be done with simple components found in an Arduino starter kit?
Like a LED and LDR, or two LEDs? 

## Demo

Could use detected beat events to trigger LEDs in sync with beat 
Demo could be exercising to increase
Can use commercial BMP monitor on wristband/smartwatch as reference

## Requirements

BPM range heartbeat. 30-200 BPM, 0.5 - 3.3 Hz
Well under line frequency 50-60Hz.
Should probably low-pass to reject that, somewhere between 6.25,12.5,25Hz (3-1 octave, giving 24 to 6 dB rejection)
Should sample at maybe 100Hz. 10 ms max aquisition time.

## Hardware
How to place the electronics?
Use some plastelina etc.

### Light sensing mechanism

Trying to use an LED as the light sensor.
See [led_light_sensor.md](./led_light_sensor.md)

# Scope

## Out of scope

Later: Integration

- Potential for integration into single board with I2C/interrupt
- Running on some small microcontroller. AtTiny etc

Later: on-device learning

- Potential of on-device learning / calibration.

Later: generalized event detection

- Can probably be generalized to other low-rate event detection problems
- Assuming adjustable parameters in the pipeline

# Background

## Prior work
Other examples of making heartbeat detector / pulse sensor

### Leonov
Someone did it with LDR. And lots of op amps. Analog comparator. No active light source.
https://www.hackster.io/104829/detecting-heart-rate-with-a-photoresistor-680b58

### Johan_Ha
Someone did it with infrared 
KY-039 / KY-03 / KY-39 IR transmissive sensor
Arduino code and DSP explanations. Incl demo video
https://projecthub.arduino.cc/Johan_Ha/8c660b94-ae6c-4b1b-b8c9-477facc50262

### PulseSensor
Great candidate for a reference design.

https://pulsesensor.com/
Is a DIY commercial board that is open hardware.
https://pulsesensor.com/pages/open-hardware
Designed to be connected to Arduino etc.
Outputs a signal conditioned analog voltage referenced around Vcc/2.
Uses an analog ambient light sensor, and a ultrabright green LED.

Has also 3d-printable thing for positioning on finger
https://www.thingiverse.com/thing:5649384
Uses a LED and a photo-diode
Uses velcro strap around finger

### Easy Pulse
https://embedded-lab.com/blog/introducing-easy-pulse-a-diy-photoplethysmographic-sensor-for-measuring-heart-rate/
https://embedded-lab.com/blog/introducing-easy-pulse-a-diy-photoplethysmographic-sensor-for-measuring-heart-rate/2/

Uses TCRT1000 reflective optical sensor.
Infrared light emitter and phototransistor placed side by side.
Enclosed inside a leaded package. Minimum effect of surrounding visible light.

Sensor output is passed through a
RC high-pass filter (HPF) to get rid of the DC component, cutoff  0.7 Hz.
and an active low-pass filter (LPF) with gain 101, cut-off frequency 2.34 Hz.
Then another stage with similar filters.

Had only 1 mV p2p at the phototransistor.
Superimposed on a 1.7 V signal.
After first stage 1V, and then 5V at second stage.

#### Easy Pulse v1.1
https://www.tindie.com/products/rajbex/easy-pulse-sensor-based-on-photoplethysmography/
https://embedded-lab.com/blog/easy-pulse-version-1-1-sensor-overview-part-1/
https://www.elecrow.com/easy-pulse-v11-p-837.html

Has 3.5mm minijack for connecting the sensor
Uses HRM-2511E transmission PPG sensor
HPF fc=0.5, LPF fc=3.4Hz

#### Easy Pulse Plugin
https://embedded-lab.com/blog/introducing-easy-pulse-plugin-breadboard-friendly-arduinochipkit-compatible-pulse-sensor/

Designed to plug into Arduino Uno etc.
Otherwise same as v1.1

#### Easy Pulse Mikro
https://embedded-lab.com/blog/easy-pulse-mikro/

#### Heart Rate Monitor 1
Uses an infrared emitter and IR receiver, connected direct to Arduino.
No analog signal conditioning.
https://www.instructables.com/Heart-Rate-Monitor-1/
band-pass filter with a passband of 1 hz - 3 hz

### PPG EduKit: An Adjustable Photoplethysmography Evaluation System for Educational Activities

IR, Red an Green LED, plus wide-spectrum photodetector (400 nm to 1000 nm).

Ambient Light Cancellation (ALC):
Ambient light leakage, i.e., photocurrent generated by ambient light
and not by the LEDs occurs during PPG signal acquisition.
Done in analog. Rest digital.

First and second order active band-pass filters are often used to filter DC components
(with cutoff frequencies as low as 0.15 Hz)
as well as high frequency noise signals (cutoff frequencies from 5 Hz up to 60 Hz).

### A Photoplethysmograph Experiment for Microcontroller Labs
2012

Separate infrared LED (SFH487) and phototransistor (SFH309FA).
Significantly simpler to apply the reflective method,
especially if the photodetector is integrated with the actuator.
Example used TCRT1000 sensor-actuator pair.

> In most cases, the DC component is removed by an analogue high-pass filter,
> then the AC signal is amplified by operational amplifiers
> to match the range and input impedance of the ADC integrated into the MCU.
> However, if the MCU has a wide dynamic range and low noise ADC (resolution range from 16 to 24 bits)
> the required signal processing can be done in the digital domain
> and the external analogue signal conditioning can be omitted
> so the sensor can be directly interfaced

C8051F350DK. 8051 MCU with 24-bit sigma-delta ADC

- high pass filtering with sub-1Hz corner frequency to remove the DC component
- low pass filtering with corner frequency of about a 20-30 Hz to remove high frequency noise
- amplification to get large enough signal, gain of 100
Shows a single op-amp option do to signal conditioning. LF,HF,gain.
But mostly.

100 hz sample rate. 16 bit.

### Grove - Finger-clip Heart Rate Sensor
https://wiki.seeedstudio.com/Grove-Finger-clip_Heart_Rate_Sensor/

Heart Rate Detection (HRD)
Using PAH8001EI-2G optical sensor. Green LED and integrated DSP.
Has an STM32 onboard

### Seedstudio - Goove Ear-clip Heart Rate Sensor
https://wiki.seeedstudio.com/Grove-Ear-clip_Heart_Rate_Sensor/
Uses a standard ear clip as the sensor.
Kyoto HRM-2511B ear-lobe clip. Transmissive mode.
Kyoto also has HRM-2511C and HRM-2511D, which are reflective mode.

Lots of details on PPG heart rate detection in
https://files.seeedstudio.com/wiki/Grove-Ear-clip_Heart_Rate_Sensor/res/PPG%20Sensor%20System.pdf

### Radar-based heartrate

TinyML radar approach
https://youtu.be/jONrpgmR4kw?t=1001
Shows 2 BPM MAE rate even with dynamic persons and postures
Sitting still, clenching hand to increase heartrate. Grows slowly

Gesture detection. Using TCN on top of CNN.
https://arxiv.org/abs/2006.16281
https://tinyradar.ethz.ch/ dataset

## Whys is green light used?

### Red Light versus Green Light, The Future of Optical Sensing in Wearable Devices

https://medium.com/bsxtechnologies/red-light-versus-green-light-74fdd5fe7027

Green light is most common for Optical Heart Rate Monitors (OHRM).
Uses process called photoplethysmography (PPG).
Green light is well absorbed by body. Also by hemoglobin.
Reduced ambient noise. 

Red light PPG sensors (also called pulse oximeters) utilize light in near-infrared spectroscopy (NIRS).

Claims that red light can measure more paramters, due to penetrating deeper in body.
Markets devices that can sense different parameters, using red light.
Such as lactate threshold and hydration/sweat. 

# Worklog

## 16.08.2023

Tested PulseSensor board. Works as documented.
Gives clear bumps for each pulse. Centered around VCC/2.
Removing the DC offset and thresholding can be good enough to measure pulse.

Tested using TCRT1000 directly connected to microcontroller.
Running at approx 50mA (3.3V and 22 ohms). 
See large changes in output when placing finger in front.
But no peaks/dips that correspond to heartbeats. Just noise.

## 19.04.2023
Arduino Playground LedSensor approach.
Tested with `ledsensor.ino`

- 11 ohm series resistor
- 5 mm clear red LED

```
condition,milliseconds
coverhands,600
ambient,180
phonescreen,50
LED direct,5
```

## 22.04.2023

Tested with `lightsensorled.ino`.

At 50 and 100 Hz, seeing very strong periodic patterns.
Seem to be independent of finger being present.
Not even able to distinguish shadows over the sensor.
Values are quite small. Could be at the ADC noise floor? Or other noise in system?
Maybe going down to 8 bit resolution could help?
Maybe reading n=5 times for both ref and sample, then taking the median?

At 25 Hz, able to distinguish different materials being in front of LED/sensor.
Seemingly able to get a heartbeat like signal also?
When doing median removal using 1 second windows, and Welch method PSD over 20 second period.
Seeing peaks in frequency spectrum at 100/200/300 BPM,
Should be indicative of 100 BPM signal.
But SNR is very low, peaks just 3-5 dB over the rest of spectrum.

# TODO

- Test at different heartrates with standard green LEDs
- Clean up Python processing code.
- Test with reference photodiode / known working sensor. TCRT1000
- Test IR LEDs
- Test ultrabright green
- Collect dataset with reference labels
- Implement pre-processing in C

MAYBE

- Try to increase sample rate again?
25 Hz seems vunerable to 50Hz aliasing

## Shopping list

5 mm clear LEDs, 30 deg angle

https://www.digikey.no/no/products/filter/led-indikasjon-frittst%C3%A5ende-diskret/105?s=N4IgjCBcoGwJxVAYygMwIYBsDOBTANCAPZQDaIALGGABxwDsIAuoQA4AuUIAyuwE4BLAHYBzEAF9CAVikRoIFJAw4CxMuBpgK9CiEJgpMAMxGpzNp0g9%2BwsZI0UjiBWix5CJSORMAGOk5YQDi5eQVEJQgAmH0iEeUVldzUvEEjYuEiIKPTacyDLazC7QgBaSOdFfgBXVU9yM0IEJnsSs3jXFQ91cub7NtBWKDA2QchIqXsYZwEAEy4SsB8s-K49EABHdgBPLnG17dZcLnRsFHFxIA

https://www.digikey.no/no/products/detail/creeled-inc/C503B-RCN-CW0Z0AA2/2341611
https://www.digikey.no/no/products/detail/creeled-inc/C503B-GCS-CY0C0792/2341581
https://www.digikey.no/no/products/detail/creeled-inc/C512A-WNN-CZ0B0152/2809666
https://www.digikey.no/no/products/detail/creeled-inc/C503B-BCS-CV0Z0462/2341549
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
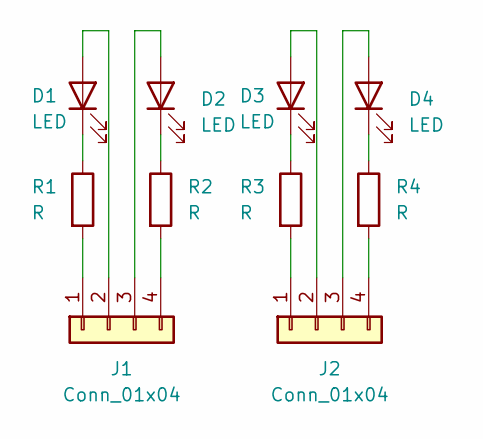
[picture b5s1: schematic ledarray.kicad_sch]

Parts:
D1, D2, D3, D4: LED; LED_0805_2012Metric_Pad1.15x1.40mm_HandSolder
J1, J2: Conn_01x04; PinHeader_1x04_P2.54mm_Vertical
R1, R2, R3, R4: R; R_0805_2012Metric_Pad1.20x1.40mm_HandSolder

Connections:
unnamed: D1.2 (A), J1.2
unnamed: D1.1 (K), R1.1
unnamed: D2.2 (A), J1.3
unnamed: D2.1 (K), R2.1
unnamed: D3.2 (A), J2.2
unnamed: D3.1 (K), R3.1
unnamed: D4.2 (A), J2.3
unnamed: D4.1 (K), R4.1
unnamed: J1.1, R1.2
unnamed: J1.4, R2.2
unnamed: J2.1, R3.2
unnamed: J2.4, R4.2

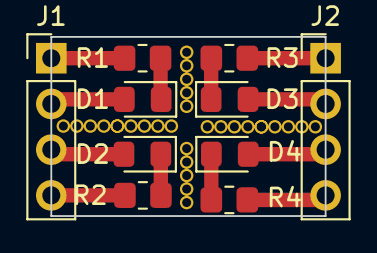
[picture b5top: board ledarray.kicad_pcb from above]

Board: 2 copper layers, 15.2 x 10.0 mm, 10 parts (0 on the bottom side), 12 nets.
